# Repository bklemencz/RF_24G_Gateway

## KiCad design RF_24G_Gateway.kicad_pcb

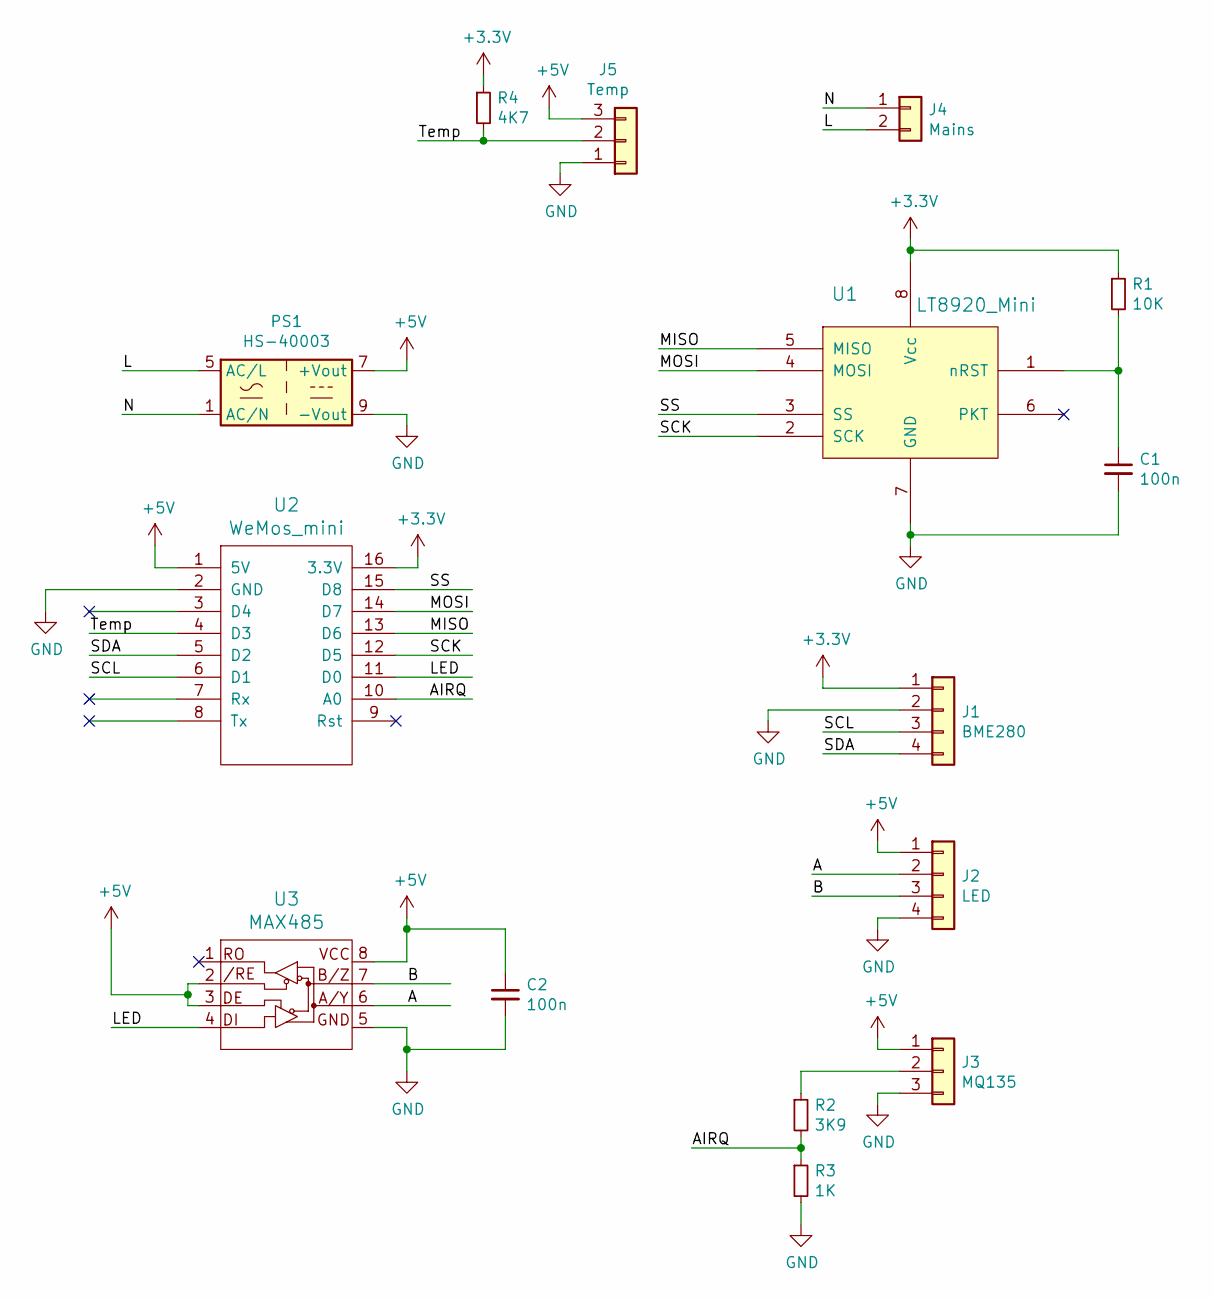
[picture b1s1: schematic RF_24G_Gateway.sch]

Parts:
C1, C2: 100n; C_0805
J1: BME280; Pin_Header_Straight_1x04_Pitch2.54mm
J2: LED; JST_B4B-XH-A_Nosilk
J3: MQ135; JST_B3B-XH-A_Nosilk
J4: Mains; mors_2p
J5: Temp; PinHeader_1x03_P2.54mm_Vertical
PS1: HS-40003; 5V700mA_ACDC
R1: 10K; R_0805
R2: 3K9; R_0805
R3: 1K; R_0805
R4: 4K7; R_0805
U1: LT8920_Mini; XY-WB_LT8920_Nosilk
U2: WeMos_mini; wemos-d1-mini-with-pin-header-and-connector
U3: MAX485; SOIC-8_3.9x4.9mm_Pitch1.27mm

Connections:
+3V3: J1.1, R1.1, R4.1, U1.8 (Vcc), U2.16 (3.3V)
+5V: C2.1, J2.1, J3.1, J5.3, PS1.7 (+Vout), U2.1 (5V), U3.2 (/RE), U3.3 (DE), U3.8 (VCC)
/A: J2.2, U3.6 (A/Y)
/AIRQ: R2.2, R3.1, U2.10 (A0)
/B: J2.3, U3.7 (B/Z)
/L: J4.2, PS1.5 (AC/L)
/LED: U2.11 (D0), U3.4 (DI)
/MISO: U1.5 (MISO), U2.13 (D6)
/MOSI: U1.4 (MOSI), U2.14 (D7)
/N: J4.1, PS1.1 (AC/N)
/SCK: U1.2 (SCK), U2.12 (D5)
/SCL: J1.3, U2.6 (D1)
/SDA: J1.4, U2.5 (D2)
/SS: U1.3 (SS), U2.15 (D8)
/Temp: J5.2, R4.2, U2.4 (D3)
GND: C1.2, C2.2, J1.2, J2.4, J3.3, J5.1, PS1.9 (-Vout), R3.2, U1.7 (GND), U2.2 (GND), U3.5 (GND)
unnamed: C1.1, R1.2, U1.1 (nRST)
unnamed: J3.2, R2.1

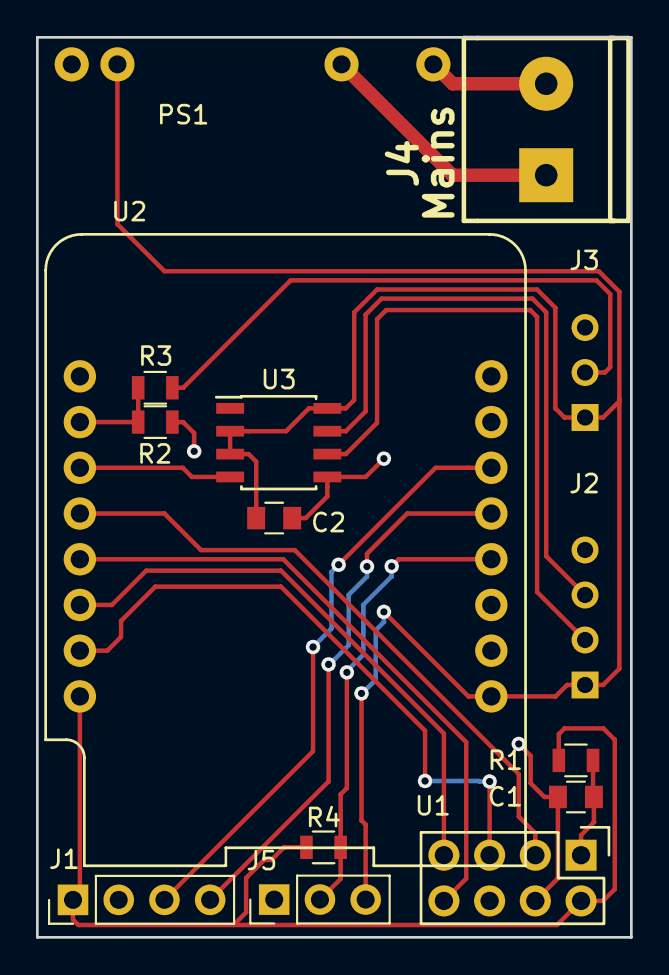
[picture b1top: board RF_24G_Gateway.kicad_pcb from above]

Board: 2 copper layers, 33.0 x 50.0 mm, 15 parts (0 on the bottom side), 18 nets.

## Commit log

2020-12-31 Gerber Removed
